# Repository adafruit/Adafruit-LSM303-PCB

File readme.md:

# PCB for the Adafruit LSM303 3-axis Compass + 3-axis Accelerometer

<a href="http://www.adafruit.com/products/1120"><br/>Click here to purchase one from the Adafruit shop</a>

He told you "Go West, young maker!" - but you don't know which way is West! Ah, if only you had this triple-axis accelerometer/magnetometer compass module. Inside are two sensors, one is a classic 3-axis accelerometer, which can tell you which direction is down towards the Earth (by measuring gravity). The other is a magnetometer that can sense where the strongest magnetic force is coming from, generally used to detect magnetic north. By combining this data you can then orient your project!

We based this breakout on the latest version of this popular sensor, the LSM303DLHC. This compact sensor uses I2C to communicate and its very easy to use. Since it's a 3.3V max chip, we added circuitry to make it 5V-safe logic and power, for easy use with either 3 or 5V microcontrollers. Simply connect VCC to +3-5V and ground to ground. Then read data from the I2C clock and data pins. There's also a Data Ready and two Interrupt pins you can use (check the LSM303 datasheet for details)

If using with an Arduino, its extra-easy to get started as we already wrote a nice little Arduino library to get you started. Simply download our library and connect the SCL pin to your Arduino's I2C clock pin, and SDA pin to your Arduino's I2C data pin and upload our test program to read out accelerometer and magnetic field data.

## License

Adafruit invests time and resources providing this open source design, 
please support Adafruit and open-source hardware by purchasing 
products from Adafruit!

Designed by Adafruit Industries.  
Creative Commons Attribution, Share-Alike license, check license.txt for more information
All text above must be included in any redistribution

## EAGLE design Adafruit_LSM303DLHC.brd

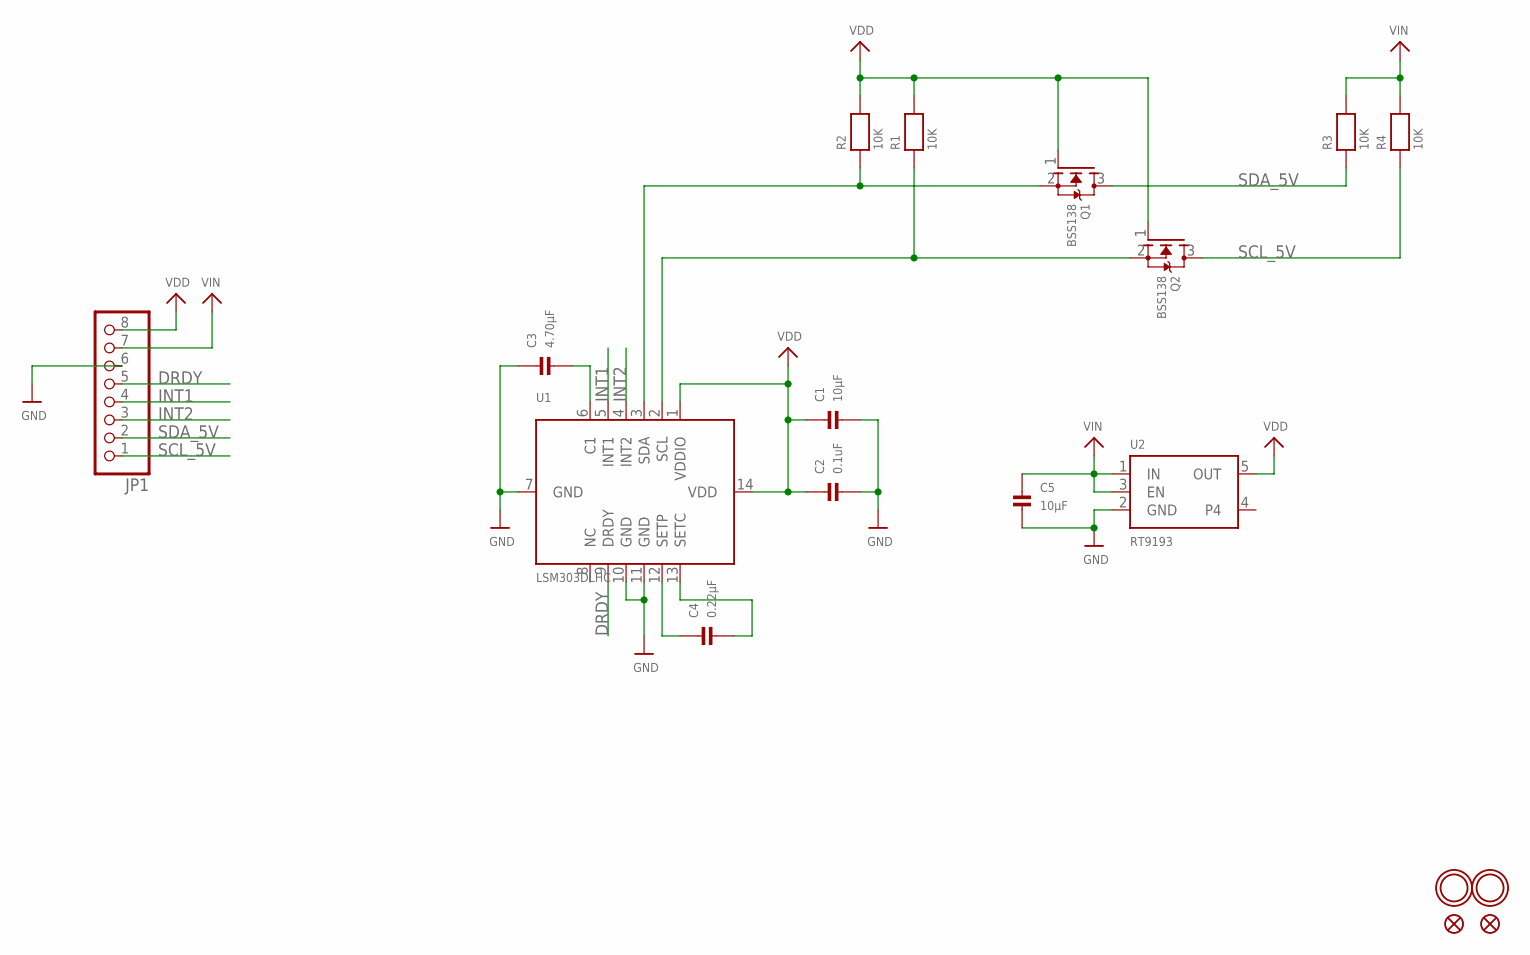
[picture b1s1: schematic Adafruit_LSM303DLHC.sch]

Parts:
C1, C5: 10µF; _0805
C2: 0.1uF; _0805
C3: 4.70µF; _0805
C4: 0.22µF; _0805
FID1, FID2: FIDUCIAL""; FIDUCIAL_1MM
JP1: HEADER-1X876MIL; 1X08_ROUND_76
Q1, Q2: BSS138; SOT23-WIDE
R1, R2, R3, R4: 10K; _0805
U1: LSM303DLHC; LGA14
U2: RT9193; SOT23-5
U$3, U$4: MOUNTINGHOLE2.5; MOUNTINGHOLE_2.5_PLATED

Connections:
DRDY: JP1.5, U1.9 (DRDY)
GND: C1.2, C2.2, C3.1, C5.2, JP1.6, U1.7 (GND), U1.10 (GND), U1.11 (GND), U2.2 (GND)
INT1: JP1.4, U1.5 (INT1)
INT2: JP1.3, U1.4 (INT2)
unnamed: Q1.2 (S), R2.1, U1.3 (SDA)
unnamed: Q2.2 (S), R1.1, U1.2 (SCL)
unnamed: C3.2, U1.6 (C1)
unnamed: C4.1, U1.12 (SETP)
unnamed: C4.2, U1.13 (SETC)
SCL_5V: JP1.1, Q2.3 (D), R4.1
SDA_5V: JP1.2, Q1.3 (D), R3.1
VDD: C1.1, C2.1, JP1.8, Q1.1 (G), Q2.1 (G), R1.2, R2.2, U1.1 (VDDIO), U1.14 (VDD), U2.5 (OUT)
VIN: C5.1, JP1.7, R3.2, R4.2, U2.1 (IN), U2.3 (EN)

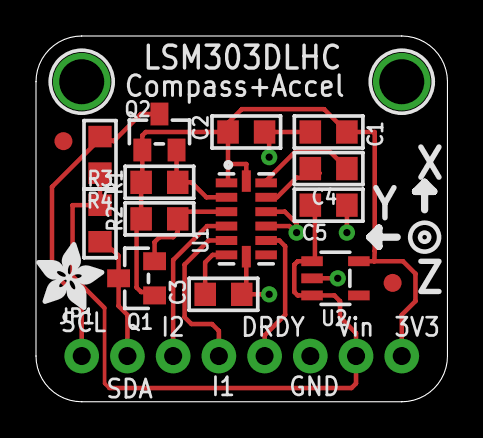
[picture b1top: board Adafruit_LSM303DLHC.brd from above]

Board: 2 copper layers, 22.9 x 20.3 mm, 19 parts (0 on the bottom side), 13 nets.

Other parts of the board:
U$17: ADAFRUIT_3.5MM

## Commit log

2013-06-19 Eagle files
2013-06-19 read
2019-04-25 readme + image
2019-04-25 readme edit

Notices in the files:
parts and their libraries:
microbuilder: This work is placed in the public domain, and may be freely used for commercial and non-commercial work with the following conditions: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
